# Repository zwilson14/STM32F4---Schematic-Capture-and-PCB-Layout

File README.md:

# STM32F4---Schematic-Capture-and-PCB-Layout
Schematic Capture and PCB Layout of a STM32F4 based microcontroller. Four layer board utilizing KiCAD w/ USB, I2C, and USART headers.
Used KiCAD for the schematic capture and board layout, and STM32CubeIDE to do the I/O planning and pin mapping.

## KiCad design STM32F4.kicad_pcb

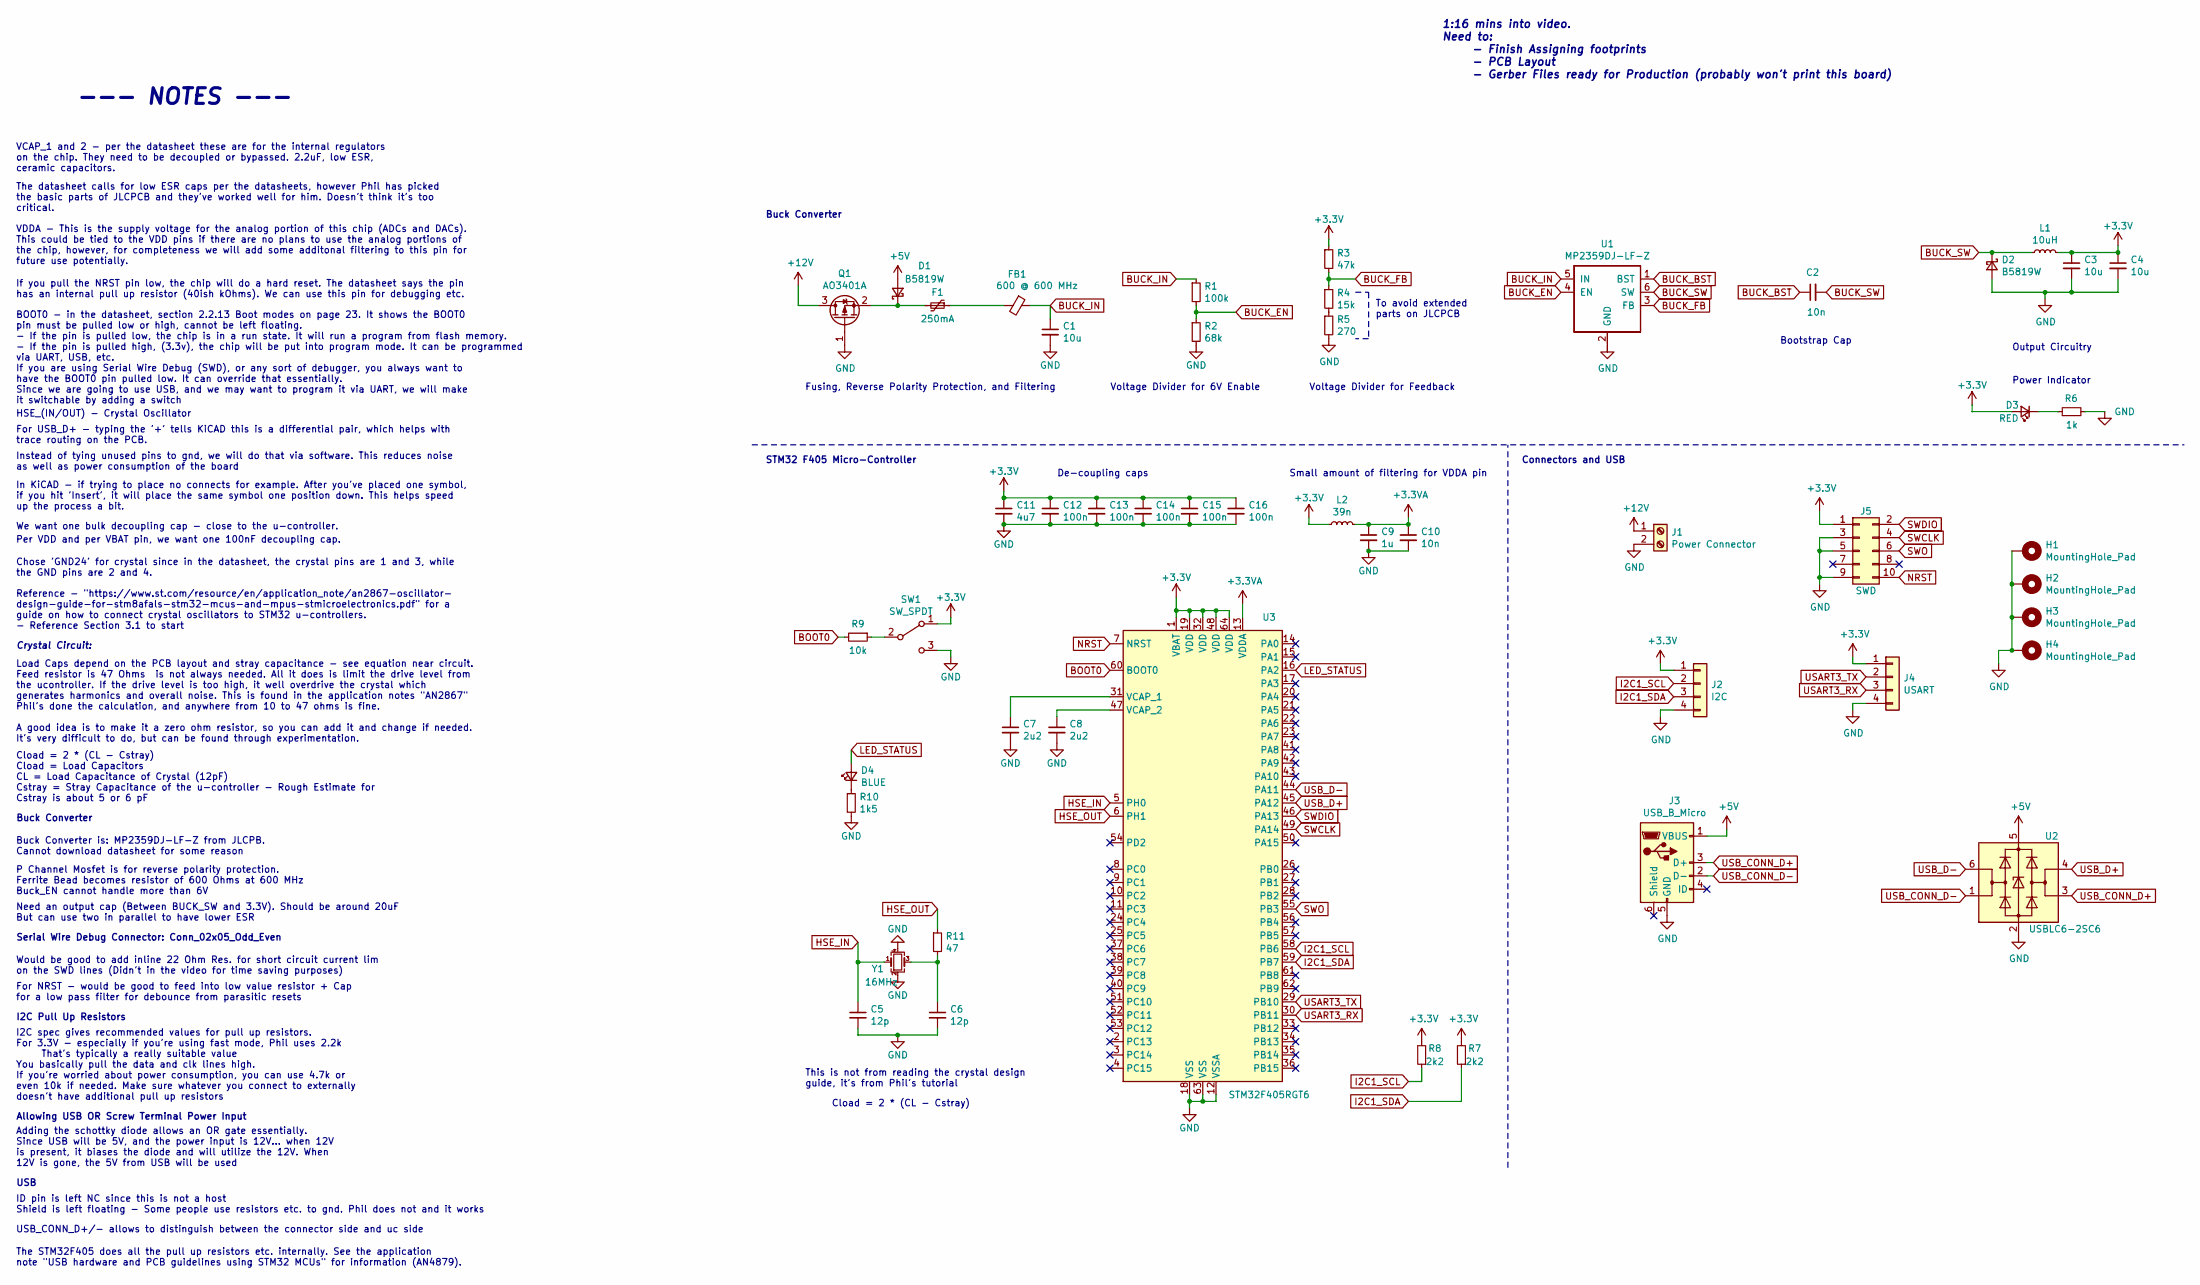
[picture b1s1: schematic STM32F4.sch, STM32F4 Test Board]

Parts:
C1, C3, C4: 10u; C_1206_3216Metric
C2: 10n; C_1206_3216Metric
C5, C6: 12p; C_0402_1005Metric
C7, C8: 2u2; C_0402_1005Metric
C9: 1u; C_0402_1005Metric
C10: 10n; C_0402_1005Metric
C11: 4u7; C_0603_1608Metric
C12, C13, C14, C15, C16: 100n; C_0402_1005Metric
D1, D2: B5819W; D_SOD-123
D3: RED; D_0603_1608Metric
D4: BLUE; D_0603_1608Metric
F1: 250mA; Fuse_1206_3216Metric
FB1: 600 @ 600 MHz; L_0805_2012Metric
H1, H2, H3, H4: MountingHole_Pad; MountingHole_4.3mm_M4_Pad_Via
J1: Power Connector; TerminalBlock_Phoenix_PT-1,5-2-3.5-H_1x02_P3.50mm_Horizontal
J2: I2C; Molex_PicoBlade_53048-0410_1x04_P1.25mm_Horizontal
J3: USB_B_Micro; USB_Micro-B_Molex-105017-0001
J4: USART; Molex_PicoBlade_53048-0410_1x04_P1.25mm_Horizontal
J5: SWD; PinHeader_2x05_P1.27mm_Vertical_SMD
L1: 10uH; L_Sunlord_MWSA0518_5.4x5.2mm
L2: 39n; L_0402_1005Metric
Q1: AO3401A; SOT-23
R1: 100k; R_0603_1608Metric
R2: 68k; R_0603_1608Metric
R3: 47k; R_0603_1608Metric
R4: 15k; R_0603_1608Metric
R5: 270; R_0603_1608Metric
R6: 1k; R_0603_1608Metric
R7, R8: 2k2; R_0603_1608Metric
R9: 10k; R_0402_1005Metric
R10: 1k5; R_0603_1608Metric
R11: 47; R_0402_1005Metric
SW1: SW_SPDT; SW_SPDT_PCM12
U1: MP2359DJ-LF-Z; SOT-23-6
U2: USBLC6-2SC6; SOT-23-6
U3: STM32F405RGT6; LQFP-64_10x10mm_P0.5mm
Y1: 16MHz; Crystal_SMD_3225-4Pin_3.2x2.5mm

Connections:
+3.3VA: C9.1, C10.1, L2.2, U3.13 (VDDA)
+3V3: C3.1, C4.1, C11.1, C12.1, C13.1, C14.1, C15.1, C16.1, D3.2 (A), J2.1, J4.1, J5.1, L1.2, L2.1, R3.1, R7.2, R8.2, SW1.1 (A), U3.1 (VBAT), U3.19 (VDD), U3.32 (VDD), U3.48 (VDD), U3.64 (VDD)
+5V: D1.2 (A), J3.1 (VBUS), U2.5 (VBUS)
+12V: J1.1, Q1.3 (D)
BOOT0: R9.2, U3.60 (BOOT0)
BUCK_BST: C2.1, U1.1 (BST)
BUCK_EN: R1.2, R2.1, U1.4 (EN)
BUCK_FB: R3.2, R4.1, U1.3 (FB)
BUCK_IN: C1.1, FB1.1, R1.1, U1.5 (IN)
BUCK_SW: C2.2, D2.1 (K), L1.1, U1.6 (SW)
GND: C1.2, C3.2, C4.2, C5.2, C6.2, C7.2, C8.2, C9.2, C10.2, C11.2, C12.2, C13.2, C14.2, C15.2, C16.2, D2.2 (A), H1.1, H2.1, H3.1, H4.1, J1.2, J2.4, J3.5 (GND), J4.4, J5.3, J5.5, J5.9, Q1.1 (G), R2.2, R5.2, R6.2, R10.2, SW1.3 (C), U1.2 (GND), U2.2 (GND), U3.12 (VSSA), U3.18 (VSS), U3.63 (VSS), Y1.2, Y1.4
HSE_IN: C5.1, U3.5 (PH0), Y1.1
HSE_OUT: R11.1, U3.6 (PH1)
I2C1_SCL: J2.2, R8.1, U3.58 (PB6)
I2C1_SDA: J2.3, R7.1, U3.59 (PB7)
LED_STATUS: D4.2 (A), U3.16 (PA2)
NRST: J5.10, U3.7 (NRST)
unnamed: C6.1, R11.2, Y1.3
unnamed: C7.1, U3.31 (VCAP_1)
unnamed: C8.1, U3.47 (VCAP_2)
unnamed: D1.1 (K), F1.2, Q1.2 (S)
unnamed: D3.1 (K), R6.1
unnamed: D4.1 (K), R10.1
unnamed: F1.1, FB1.2
unnamed: R4.2, R5.1
unnamed: R9.1, SW1.2 (B)
SWCLK: J5.4, U3.49 (PA14)
SWDIO: J5.2, U3.46 (PA13)
SWO: J5.6, U3.55 (PB3)
USART3_RX: J4.3, U3.30 (PB11)
USART3_TX: J4.2, U3.29 (PB10)
USB_CONN_D+: J3.3 (D+), U2.3 (I/O2)
USB_CONN_D-: J3.2 (D-), U2.1 (I/O1)
USB_D+: U2.4 (I/O2), U3.45 (PA12)
USB_D-: U2.6 (I/O1), U3.44 (PA11)

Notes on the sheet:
VDDA - This is the supply voltage for the analog portion of this chip (ADCs and DACs). This could be tied to the VDD pins if there are no plans to use the analog portions of the chip, however, for completeness we will add some additonal filtering to this pin for future use potentially.
VCAP_1 and 2 - per the datasheet these are for the internal regulators on the chip. They need to be decoupled or bypassed. 2.2uF, low ESR, ceramic capacitors.
The datasheet calls for low ESR caps per the datasheets, however Phil has picked the basic parts of JLCPCB and they've worked well for him. Doesn't think it's too critical.
If you pull the NRST pin low, the chip will do a hard reset. The datasheet says the pin has an internal pull up resistor (40ish kOhms). We can use this pin for debugging etc.
HSE_(IN/OUT) - Crystal Oscillator
For USB_D+ - typing the '+' tells KiCAD this is a differential pair, which helps with trace routing on the PCB.
Instead of tying unused pins to gnd, we will do that via software. This reduces noise as well as power consumption of the board
In KiCAD - if trying to place no connects for example. After you've placed one symbol, if you hit 'Insert', it will place the same symbol one position down. This helps speed up the process a bit.
We want one bulk decoupling cap - close to the u-controller.
Per VDD and per VBAT pin, we want one 100nF decoupling cap.
De-coupling caps
Cload = 2 * (CL - Cstray)
Crystal Circuit:
BOOT0 - in the datasheet, section 2.2.13 Boot modes on page 23. It shows the BOOT0 pin must be pulled low or high, cannot be left floating. - If the pin is pulled low, the chip is in a run state. It will run a program from flash memory. - If the pin is pulled high, (3.3v), the chip will be put into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
Small amount of filtering for VDDA pin
STM32 F405 Micro-Controller
Buck Converter
To avoid extended parts on JLCPCB
Fusing, Reverse Polarity Protection, and Filtering
Voltage Divider for 6V Enable
Voltage Divider for Feedback
Bootstrap Cap
Output Circuitry
Would be good to add inline 22 Ohm Res. for short circuit current lim on the SWD lines (Didn't in the video for time saving purposes)
For NRST - would be good to feed into low value resistor + Cap for a low pass filter for debounce from parasitic resets
Serial Wire Debug Connector: Conn_02x05_Odd_Even
Need an output cap (Between BUCK_SW and 3.3V). Should be around 20uF But can use two in parallel to have lower ESR
P Channel Mosfet is for reverse polarity protection. Ferrite Bead becomes resistor of 600 Ohms at 600 MHz Buck_EN cannot handle more than 6V
Buck Converter is: MP2359DJ-LF-Z from JLCPB. Cannot download datasheet for some reason
Load Caps depend on the PCB layout and stray capacitance - see equation near circuit. Feed resistor is 47 Ohms ~ is not always needed. All it does is limit the drive level from the ucontroller. If the drive level is too high, it well overdrive the crystal which generates harmonics and overall noise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
Cload = 2 * (CL - Cstray) Cload = Load Capacitors CL = Load Capacitance of Crystal (12pF) Cstray = Stray Capacitance of the u-controller - Rough Estimate for Cstray is about 5 or 6 pF
This is not from reading the crystal design guide, it's from Phil's tutorial
Reference - "https://www.st.com/resource/en/application_note/an2867-oscillator- design-guide-for-stm8afals-stm32-mcus-and-mpus-stmicroelectronics.pdf" for a guide on how to connect crystal oscillators to STM32 u-controllers. - Reference Section 3.1 to start
Chose 'GND24' for crystal since in the datasheet, the crystal pins are 1 and 3, while the GND pins are 2 and 4.
I2C Pull Up Resistors
I2C spec gives recommended values for pull up resistors. For 3.3V - especially if you're using fast mode, Phil uses 2.2k That's typically a really suitable value You basically pull the data and clk lines high. If you're worried about power consumption, you can use 4.7k or even 10k if needed. Make s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
Allowing USB OR Screw Terminal Power Input
Adding the schottky diode allows an OR gate essentially. Since USB will be 5V, and the power input is 12V... when 12V is present, it biases the diode and will utilize the 12V. When 12V is gone, the 5V from USB will be used
USB
ID pin is left NC since this is not a host Shield is left floating - Some people use resistors etc. to gnd. Phil does not and it works

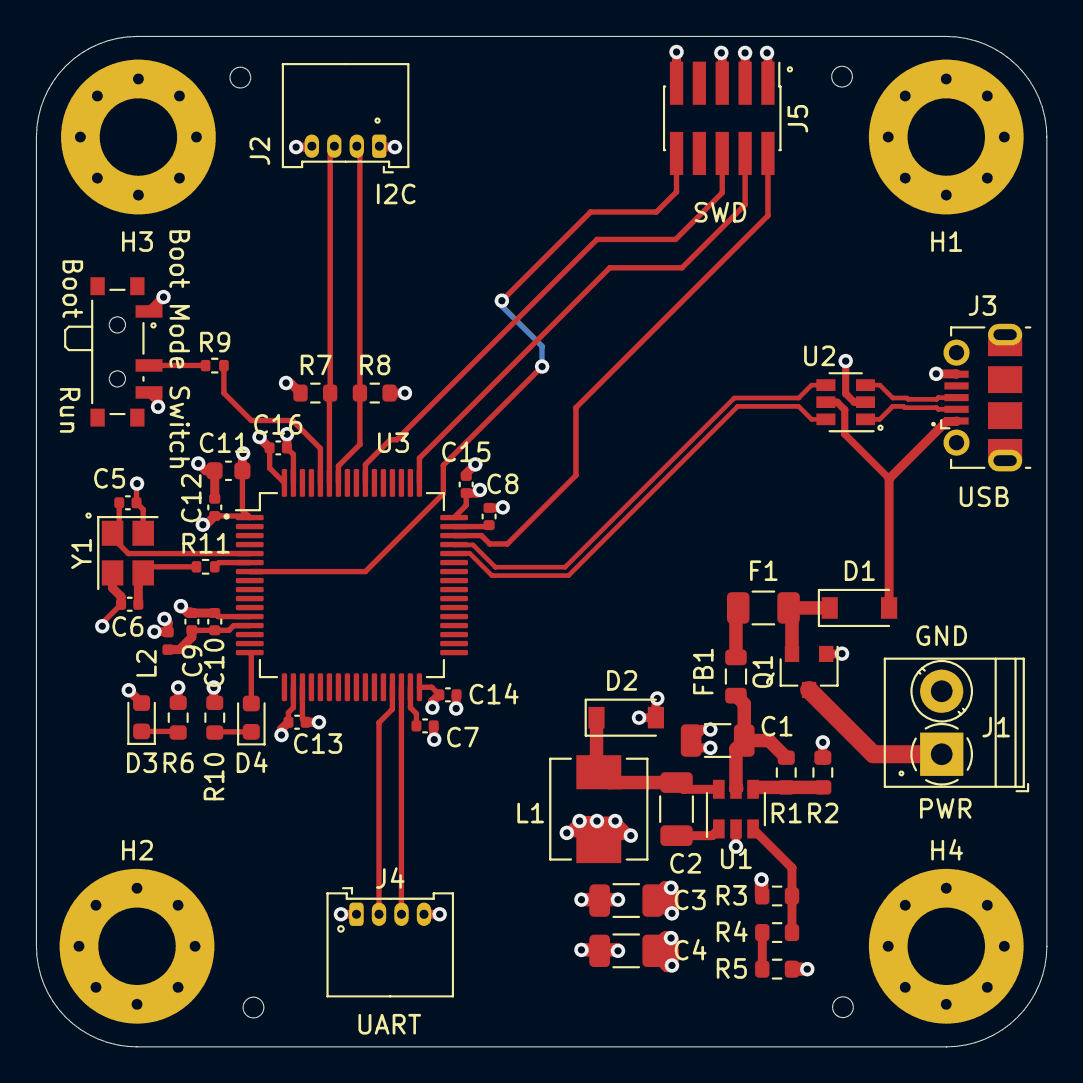
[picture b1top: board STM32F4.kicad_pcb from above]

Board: 4 copper layers, 56.1 x 56.1 mm, 50 parts (0 on the bottom side), 35 nets.

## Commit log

2025-01-10 Added files
2025-01-10 Attempt to get project icon
2025-01-10 more info on readme
